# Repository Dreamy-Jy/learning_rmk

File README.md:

# Learning RMK

This project is an account of part of the effort I put into developing context to contribute the [RMK Project](rmk.rs)

**Folder Structure:**

- [`./docs/`](docs/) - a set of writing where I chart my understandings
- [`./programs/`](programs/) - a set programs I wrote to develop understanding
- [`./hardware/`](hardware/) - a [KiCAD](https://www.kicad.org/) project for the micro pad I created as example hardware

## Folder Overviews

### [`./docs/`](docs/)

| Document Status                                                        | Title                                         | Link To File                                                             | Description                                                                                                     |
| ---------------------------------------------------------------------- | --------------------------------------------- | ------------------------------------------------------------------------ | --------------------------------------------------------------------------------------------------------------- |
|       | RMK Workflows                                 | [`docs/rmk_contributor_workflows.md`](docs/rmk_contributor_workflows.md) | A living document of workflows discovered working with RMK as firmware creator and contributor.                 |
|   | Embedded Heuristics: Getting Started          | [`docs/heuristics_blinky.md`](docs/heuristics_blinky.md)                 | Wrote blinky LED. Chronicle of Embedded Systems intuition developed doing that.                                 |
|  | TBD                                           | [`docs/heuristics_micropad.md`](docs/heuristics_blinky.md)               | Wrote a mircopad keyboard. Chronicle of Embedded Systems intuition developed doing that.                        |
|       | WT[^1]: Async + Atomic Rust Overview          | Not yet                                                                  | Expanding my understanding of concurrency by writing an Async runtime and learning atomics.                     |
|       | WT: Just Enough Macros For RMK                | Not yet                                                                  | Only learning just enough of Rust's macro system to develop RMK.<br><br>Written in parallel with other content. |
|       | WT: RMK Codebase Overview                     | Not yet                                                                  | An overview of RMK's codebase at version TBD.                                                                   |
|       | WT: Embassy Ecosystem and Ergonomics Overview | Not yet                                                                  | An overview of embassy's ecosystem, with a emphasis on api's used by RMK.                                       |

### [`./programs/`](programs/)

**TLDR:**

- 1 Programming Language
  - Rust
- 2 Boards
  - [RP Pico 1](https://www.raspberrypi.com/products/raspberry-pi-pico/)([RP2040](https://www.raspberrypi.com/products/rp2040/))
  - [nice!nano](https://nicekeyboards.com/nice-nano)([nRF52840](https://www.nordicsemi.com/Products/nRF52840))
- 3 Target Functions
  - Blinky LED
  - Switch testing
  - Micropad keyboard
- 4 Rust Projects
  - [`./programs/nrf52840_blinky/`](programs/nrf52840_blinky/) - Blinky LED on a nRF2040
  - [`./programs/rp2040_blinky/`](programs/rp2040_blinky/) - Blinky LED on a RP2040
  - [`./programs/rp2040_micropad/`](programs/rp2040_micropad) - Switch Tester, and Mircopad Keyboard on a RP2040
  - [`./programs/rp2040_rmk_micropad/`](programs/rp2040_rmk_micropad) - Mircopad Keyboard on a RP2040
- 9 Programs Written
  - [`./programs/nrf52840_blinky/src/bin/async_blinky.rs`](programs/nrf52840_blinky/src/bin/async_blinky.rs) - Async Blinky LED on a nRF52840
  - [`./programs/nrf52840_blinky/src/bin/sync_blinky.rs`](programs/nrf52840_blinky/src/bin/sync_blinky.rs) - Sync Blinky LED on a nRF52840
  - [`./programs/rp2040_blinky/src/bin/async_blinky.rs`](programs/rp2040_blinky/src/bin/async_blinky.rs) - Async Blinky LED on a RP2040
  - [`./programs/rp2040_blinky/src/bin/sync_blinky.rs`](programs/rp2040_blinky/src/bin/sync_blinky.rs) - Sync Blinky LED on a RP2040
  - [`./programs/rp2040_micropad/src/bin/matrix_tester_embassy.rs`](programs/rp2040_micropad/src/bin/matrix_tester_embassy.rs) - Switch tester
  - [`./programs/rp2040_micropad/src/bin/matrix_tester_rmk.rs`](programs/rp2040_micropad/src/bin/matrix_tester_rmk.rs) - Switch tester written with rmk
  - [`./programs/rp2040_micropad/src/bin/usb_embassy.rs`](programs/rp2040_micropad/src/bin/usb_embassy.rs) - Micropad Keyboard
  - [`./programs/rp2040_rmk_micropad/src/bin/manual.rs`](programs/rp2040_rmk_micropad/src/bin/manual.rs) - Micropad Keyboard made with RMK via manual implementation
  - [`./programs/rp2040_rmk_micropad/src/bin/toml.rs`](programs/rp2040_rmk_micropad/src/bin/toml.rs) - Micropad Keyboard made with RMK via config file implementation

### ['./hardware/'](hardware/)

**NOTICE:**

- I've provide no documentation for this part of the project. Interested parties are responsible for their own understanding
- Thank you to [NYC Resistor](https://www.nycresistor.com/) For helping to put together the board

**TLDR:**

| Schematic                                              | PCB                                        | 3D Model                                             | Real Device                                                  |
| ------------------------------------------------------ | ------------------------------------------ | ---------------------------------------------------- | ------------------------------------------------------------ |
|  |  |  |  |

[^1]: WT = Working Title

REST API
Protocol

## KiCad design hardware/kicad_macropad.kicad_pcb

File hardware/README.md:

# './hardware/'

**NOTICE:**

- I've provide no documentation for this part of the project. Interested parties are responsible for their own understanding
- Thank you to [NYC Resistor](https://www.nycresistor.com/) For helping to put together the board

**TLDR:**

|Schematic|PCB|3D Model|Real Device|
|---------|---|--------|-----------|
|||||

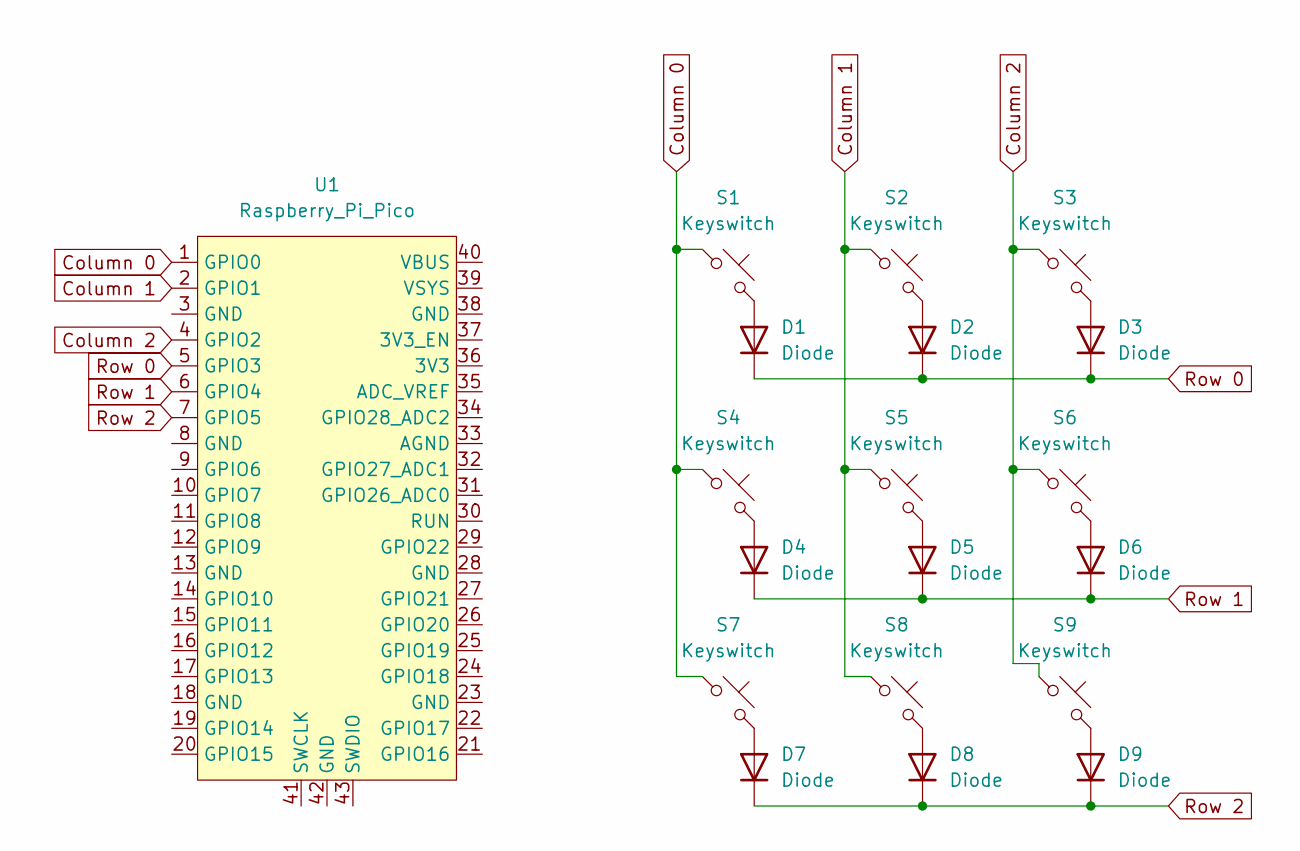
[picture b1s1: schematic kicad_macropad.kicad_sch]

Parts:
D1, D2, D3, D4, D5, D6, D7, D8, D9: Diode; D_SOD-523
S1, S2, S3, S4, S5, S6, S7, S8, S9: Keyswitch; Cherry_ULP_SMD
U1: Raspberry_Pi_Pico

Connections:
Column 0: S1.1, S4.1, S7.1, U1.1 (GPIO0)
Column 1: S2.1, S5.1, S8.1, U1.2 (GPIO1)
Column 2: S3.1, S6.1, S9.1, U1.4 (GPIO2)
unnamed: D1.2 (A), S1.2
unnamed: D2.2 (A), S2.2
unnamed: D3.2 (A), S3.2
unnamed: D4.2 (A), S4.2
unnamed: D5.2 (A), S5.2
unnamed: D6.2 (A), S6.2
unnamed: D7.2 (A), S7.2
unnamed: D8.2 (A), S8.2
unnamed: D9.2 (A), S9.2
Row 0: D1.1 (K), D2.1 (K), D3.1 (K), U1.5 (GPIO3)
Row 1: D4.1 (K), D5.1 (K), D6.1 (K), U1.6 (GPIO4)
Row 2: D7.1 (K), D8.1 (K), D9.1 (K), U1.7 (GPIO5)

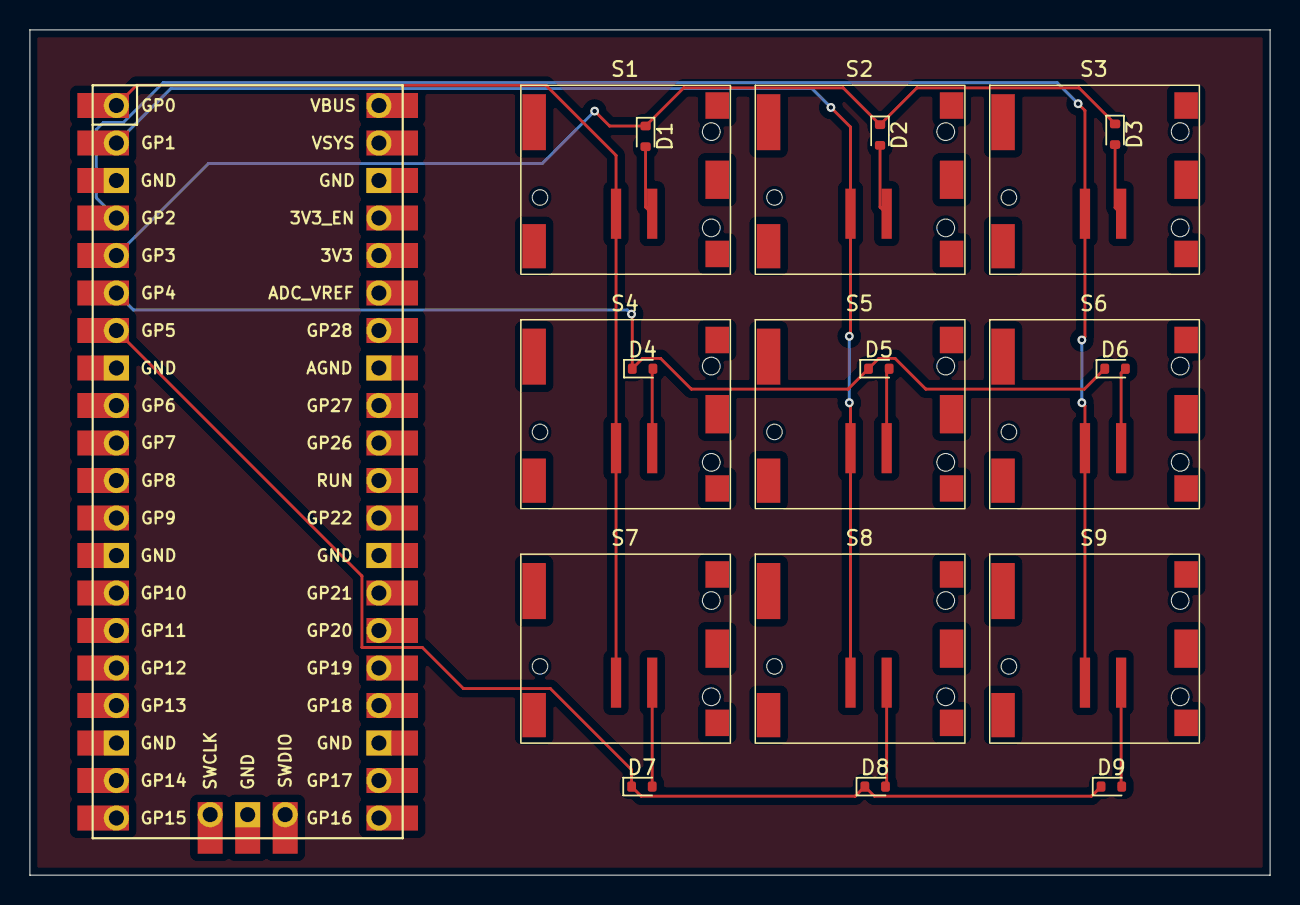
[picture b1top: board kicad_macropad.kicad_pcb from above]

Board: 2 copper layers, 84.0 x 57.2 mm, 19 parts (0 on the bottom side), 15 nets.

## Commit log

2025-11-01 checkpoint: initial commit
2025-11-01 docs: changed readme title
2025-11-01 docs: add photos and more READMEs
2025-11-02 docs: add completed article and update docs
2025-11-03 checkpoint: add hardware for project
2025-11-05 checkpoint: add nrf52840 blinky
2025-11-06 checkpoint: add rp2040 blinky
2025-11-07 checkpoint: add rp2040 micropad
2025-11-08 checkpoint: add rp2040 rmk micropad
2025-11-10 checkpoint: add docs folder
